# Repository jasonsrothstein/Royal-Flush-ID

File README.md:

# Royal-Flush-ID
Purdue University ECE 477 
Spring 2019 Senior Design 
Group 21

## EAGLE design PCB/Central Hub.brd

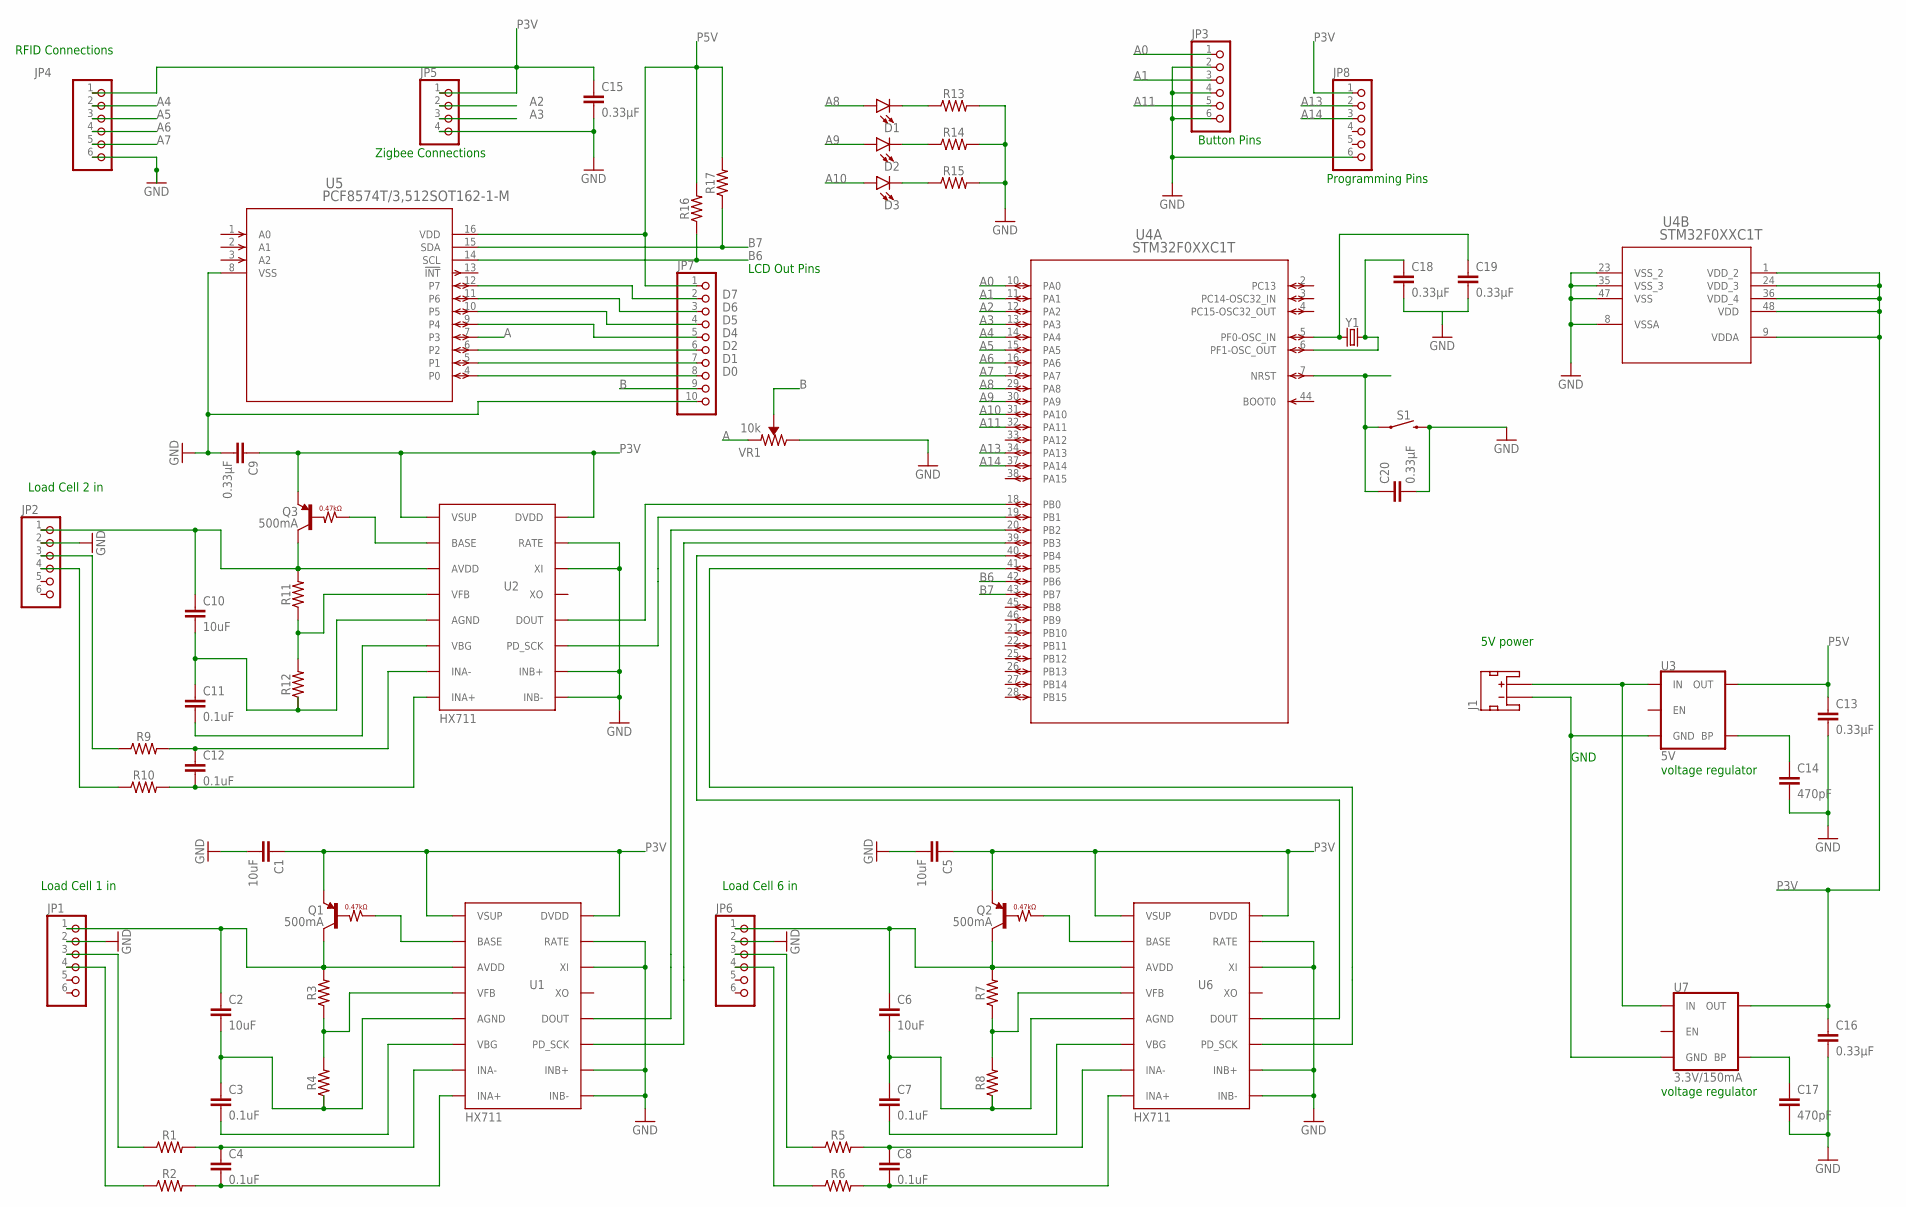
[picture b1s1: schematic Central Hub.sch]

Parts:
C1, C2, C5, C6, C10: 10uF; 0603
C3, C4, C7, C8, C11, C12: 0.1uF; 0603
C9, C13, C15, C16, C18, C19, C20: 0.33µF; 0805
C14, C17: 470pF; 0603
D1, D2, D3: LED5MM; LED_5MM
J1: JST_2MM_MALE; JST-2-SMD
JP1, JP2, JP3, JP4, JP6, JP8: PINHD-1X6; 1X06
JP5: PINHD-1X4; 1X04
JP7: PINHD-1X10; 1X10
Q1, Q2, Q3: 500mA; SOT23-3
R1, R2, R3, R4, R5, R6, R7, R8, R9, R10, R11, R12, R13, R14, R15, R16, R17: 0603
S1: MOMENTARY-SWITCH-SPST-SMD-5.2MM; TACTILE_SWITCH_SMD_5.2MM
U1, U2, U6: HX711; SO16
U3: 5V; SOT23-5
U4: STM32F0XXC1T; LQFP48-7X7MM
U5: PCF8574T/3,512SOT162-1-M; SOT162-1-M
U7: 3.3V/150mA; SOT23-5
VR1: 10k; TRIMPOT-PTH-3386U
Y1: CRYSTALPTH-HC49US; HC49US

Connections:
A: U5.7 (P3), VR1.1 (CCW)
A0: JP3.1, U4.10 (PA0)
A1: JP3.3, U4.11 (PA1)
A2: JP5.2, U4.12 (PA2)
A3: JP5.3, U4.13 (PA3)
A4: JP4.2, U4.14 (PA4)
A5: JP4.3, U4.15 (PA5)
A6: JP4.4, U4.16 (PA6)
A7: JP4.5, U4.17 (PA7)
A8: D1.A, U4.29 (PA8)
A9: D2.A, U4.30 (PA9)
A10: D3.A, U4.31 (PA10)
A11: JP3.5, U4.32 (PA11)
A13: JP8.2, U4.34 (PA13)
A14: JP8.3, U4.37 (PA14)
B: JP7.9, VR1.2 (WIPER)
B6: R16.1, U4.42 (PB6), U5.14 (SCL)
B7: R17.1, U4.43 (PB7), U5.15 (SDA)
D0: JP7.8, U5.4 (P0)
D1: JP7.7, U5.5 (P1)
D2: JP7.6, U5.6 (P2)
D4: JP7.5, U5.9 (P4)
D5: JP7.4, U5.10 (P5)
D6: JP7.3, U5.11 (P6)
D7: JP7.2, U5.12 (P7)
GND: C1.2, C5.2, C9.2, C13.2, C14.2, C15.2, C16.2, C17.2, C18.2, C19.2, C20.2, JP1.2, JP2.2, JP3.2, JP3.4, JP3.6, JP4.6, JP5.4, JP6.2, JP7.10, JP8.6, R13.2, R14.2, R15.2, S1.3 (2), U1.9 (INB-), U1.10 (INB+), U1.14 (XI), U1.15 (RATE), U2.9 (INB-), U2.10 (INB+), U2.14 (XI), U2.15 (RATE), U4.8 (VSSA), U4.23 (VSS_2), U4.35 (VSS_3), U4.47 (VSS), U5.8 (VSS), U6.9 (INB-), U6.10 (INB+), U6.14 (XI), U6.15 (RATE), VR1.3 (CW)
unnamed: C20.1, S1.1, U4.7 (NRST)
unnamed: JP1.3, R1.1
unnamed: JP1.4, R2.1
unnamed: C4.1, R1.2, U1.7 (INA-)
unnamed: C4.2, R2.2, U1.8 (INA+)
unnamed: Q1.1 (B), U1.2 (BASE)
unnamed: C2.1, JP1.1, Q1.3 (C), R3.2, U1.3 (AVDD)
unnamed: C2.2, C3.1, R4.1, U1.5 (AGND)
unnamed: R3.1, R4.2, U1.4 (VFB)
unnamed: C3.2, U1.6 (VBG)
unnamed: JP6.3, R5.1
unnamed: JP6.4, R6.1
unnamed: C8.1, R5.2, U6.7 (INA-)
unnamed: C8.2, R6.2, U6.8 (INA+)
unnamed: Q2.1 (B), U6.2 (BASE)
unnamed: C6.1, JP6.1, Q2.3 (C), R7.2, U6.3 (AVDD)
unnamed: C6.2, C7.1, R8.1, U6.5 (AGND)
unnamed: R7.1, R8.2, U6.4 (VFB)
unnamed: C7.2, U6.6 (VBG)
unnamed: C19.1, U4.5 (PF0-OSC_IN), Y1.1
unnamed: C18.1, U4.6 (PF1-OSC_OUT), Y1.2
unnamed: JP2.3, R9.1
unnamed: JP2.4, R10.1
unnamed: C12.1, R9.2, U2.7 (INA-)
unnamed: C12.2, R10.2, U2.8 (INA+)
unnamed: Q3.1 (B), U2.2 (BASE)
unnamed: C10.1, JP2.1, Q3.3 (C), R11.2, U2.3 (AVDD)
unnamed: C10.2, C11.1, R12.1, U2.5 (AGND)
unnamed: R11.1, R12.2, U2.4 (VFB)
unnamed: C11.2, U2.6 (VBG)
unnamed: J1.1 (-), U3.2 (GND), U7.2 (GND)
unnamed: C17.1, U7.4 (BP)
unnamed: C14.1, U3.4 (BP)
unnamed: J1.2 (+), U3.1 (IN), U7.1 (IN)
unnamed: D1.K (C), R13.1
unnamed: D2.K (C), R14.1
unnamed: D3.K (C), R15.1
unnamed: U4.41 (PB5), U6.11 (PD_SCK)
unnamed: U4.40 (PB4), U6.12 (DOUT)
unnamed: U1.11 (PD_SCK), U4.39 (PB3)
unnamed: U1.12 (DOUT), U4.20 (PB2)
unnamed: U2.11 (PD_SCK), U4.19 (PB1)
unnamed: U2.12 (DOUT), U4.18 (PB0)
P3V: C1.1, C5.1, C9.1, C15.1, C16.1, JP4.1, JP5.1, JP8.1, Q1.2 (E), Q2.2 (E), Q3.2 (E), U1.1 (VSUP), U1.16 (DVDD), U2.1 (VSUP), U2.16 (DVDD), U4.1 (VDD_2), U4.9 (VDDA), U4.24 (VDD_3), U4.36 (VDD_4), U4.48 (VDD), U6.1 (VSUP), U6.16 (DVDD), U7.5 (OUT)
P5V: C13.1, JP7.1, R16.2, R17.2, U3.5 (OUT), U5.16 (VDD)

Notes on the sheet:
Zigbee Connections
RFID Connections
voltage regulator
5V power
GND
Programming Pins
Button Pins
LCD Out Pins
Load Cell 2 in
Load Cell 1 in
Load Cell 6 in

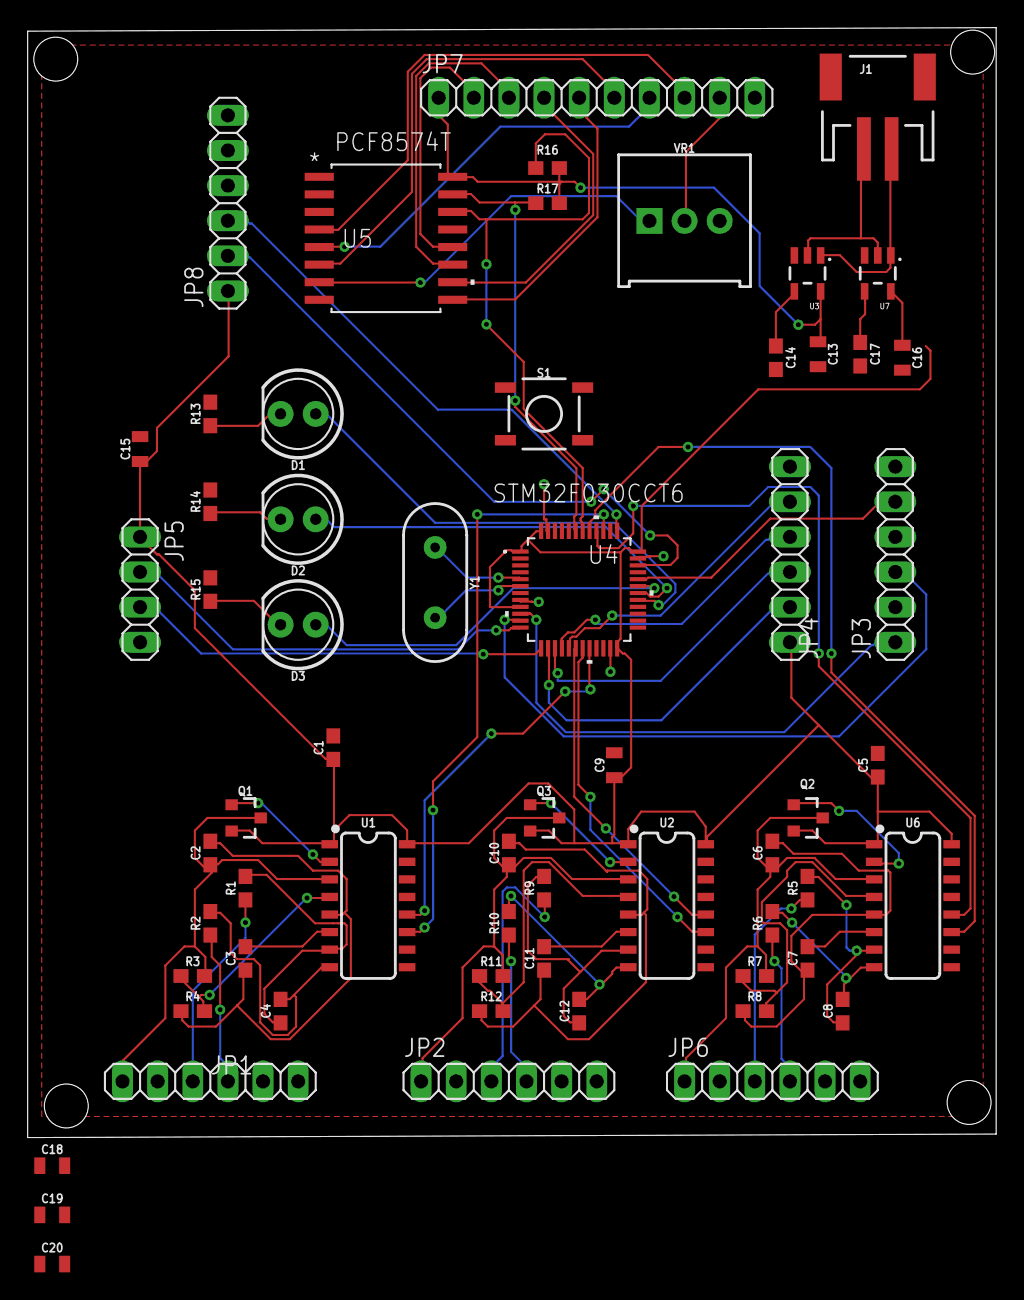
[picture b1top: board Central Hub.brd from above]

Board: 2 copper layers, 70.0 x 80.3 mm, 62 parts (0 on the bottom side), 71 nets.

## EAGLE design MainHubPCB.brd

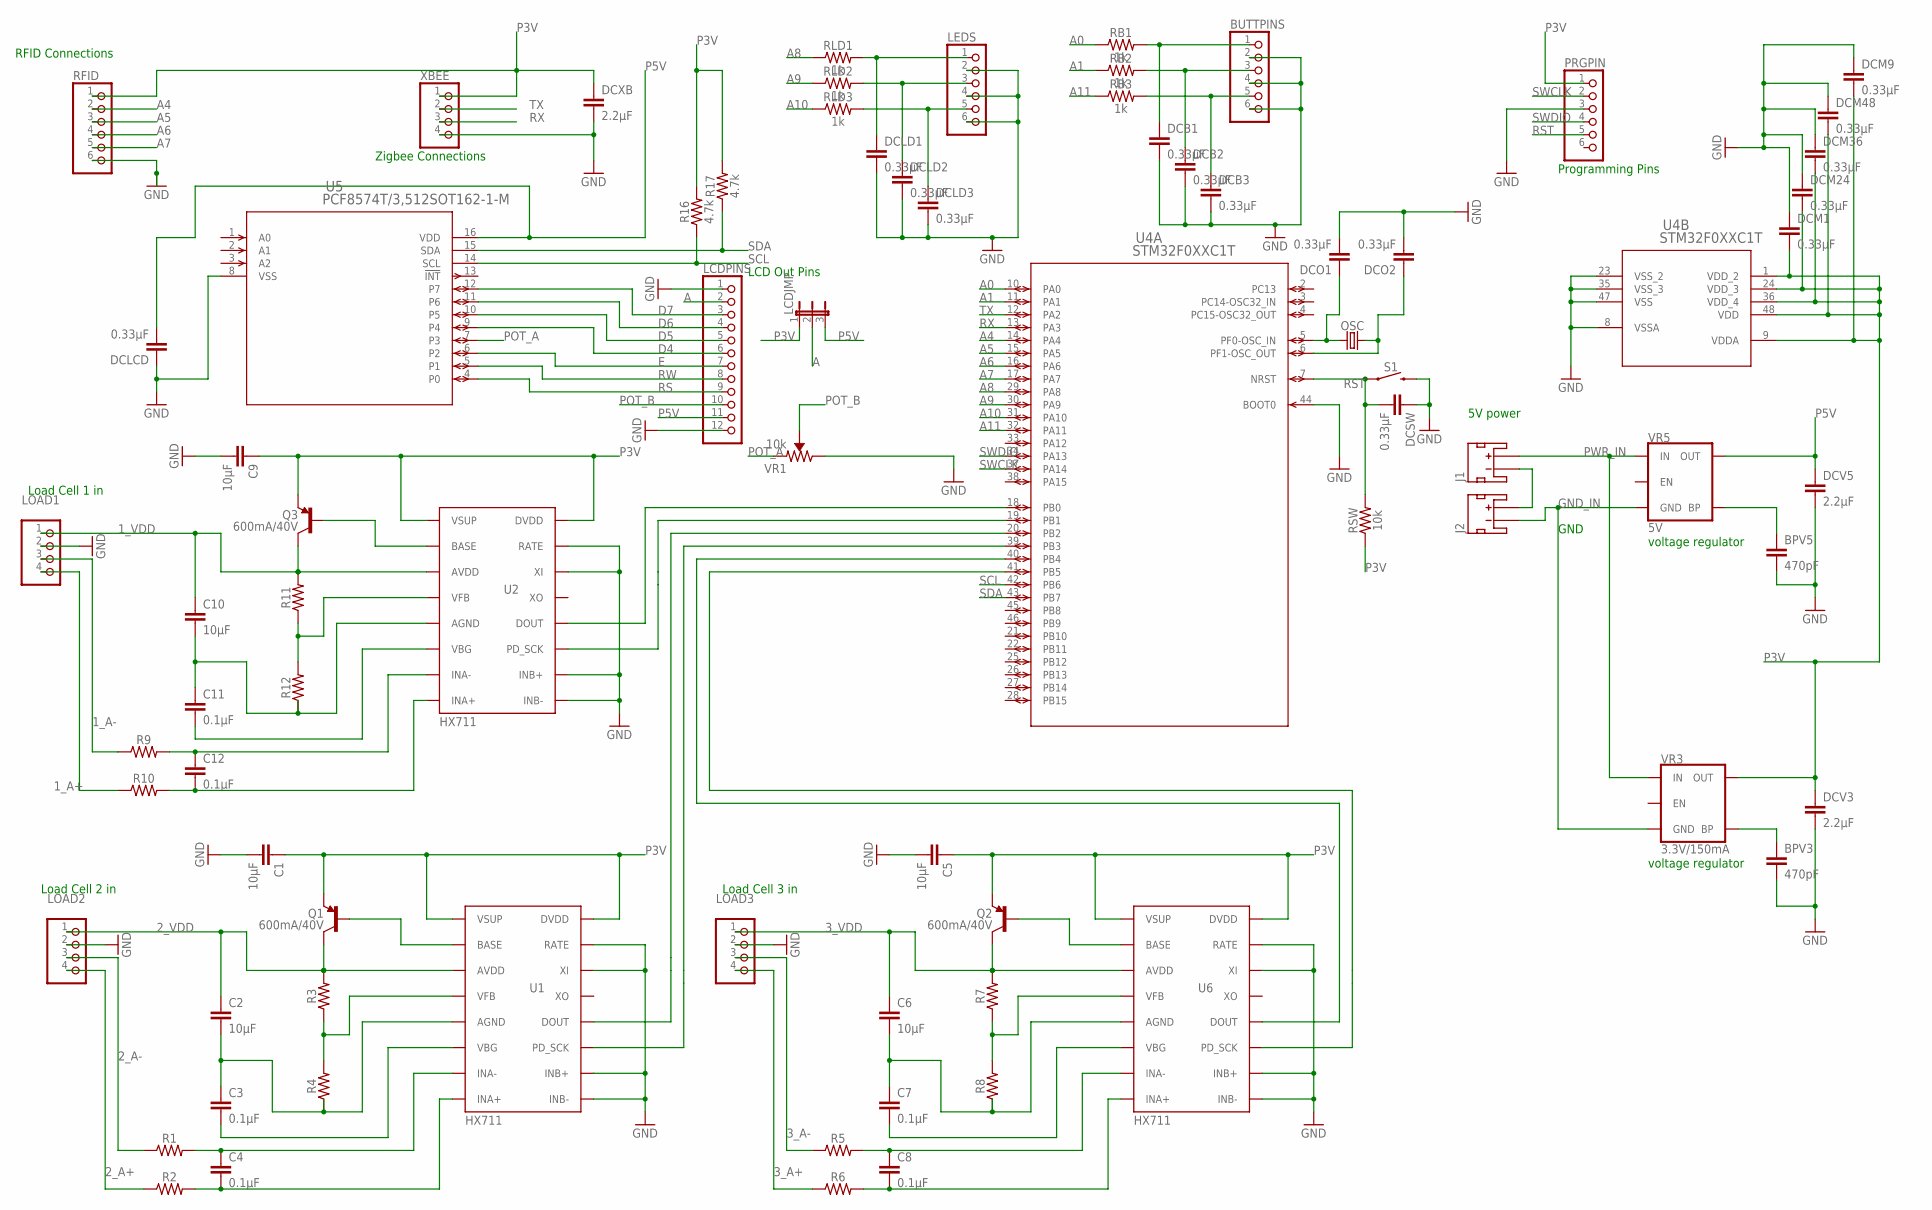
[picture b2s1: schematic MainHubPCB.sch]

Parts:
BPV3, BPV5: 470pF; 0805
BUTTPINS: PINHD-1X6; 1X06
C1, C2, C5, C6, C9, C10: 10µF; 0805
C3, C4, C7, C8, C11, C12: 0.1µF; 0805
DCB1, DCB2, DCB3: 0.33µF; 0805
DCLCD: 0.33µF; 0805
DCLD1, DCLD2, DCLD3: 0.33µF; 0805
DCM1, DCM9, DCM24, DCM36, DCM48: 0.33µF; 0805
DCO1, DCO2: 0.33µF; 0805
DCSW: 0.33µF; 0805
DCV3, DCV5: 2.2µF; 0805
DCXB: 2.2µF; 0805
J1, J2: JST_2MM_MALE; JST-2-SMD
LCDJMP: JP2E; JP2
LCDPINS: PINHD-1X12; 1X12
LEDS: PINHD-1X6; 1X06
LOAD1, LOAD2, LOAD3: PINHD-1X4; 1X04
OSC: CRYSTALPTH-HC49US; HC49US
PRGPIN: PINHD-1X6; 1X06
Q1, Q2, Q3: 600mA/40V; SOT23-3
R1, R2, R3, R4, R5, R6, R7, R8, R9, R10, R11, R12: 0805
R16, R17: 4.7k; 0805
RB1, RB2, RB3: 1k; 0805
RFID: PINHD-1X6; 1X06
RLD1, RLD2, RLD3: 1k; 0805
RSW: 10k; 0805
S1: MOMENTARY-SWITCH-SPST-SMD-5.2MM; TACTILE_SWITCH_SMD_5.2MM
U1, U2, U6: HX711; SO16
U4: STM32F0XXC1T; LQFP48-7X7MM
U5: PCF8574T/3,512SOT162-1-M; SOT162-1-M
VR1: 10k; TRIMPOT-PTH-3386U
VR3: 3.3V/150mA; SOT23-5
VR5: 5V; SOT23-5
XBEE: PINHD-1X4; 1X04

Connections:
1_A+: LOAD1.4, R10.1
1_A-: LOAD1.3, R9.1
1_VDD: C10.1, LOAD1.1, Q3.3 (C), R11.2, U2.3 (AVDD)
2_A+: LOAD2.4, R2.1
2_A-: LOAD2.3, R1.1
2_VDD: C2.1, LOAD2.1, Q1.3 (C), R3.2, U1.3 (AVDD)
3_A+: LOAD3.4, R6.1
3_A-: LOAD3.3, R5.1
3_VDD: C6.1, LOAD3.1, Q2.3 (C), R7.2, U6.3 (AVDD)
A: LCDJMP.2, LCDPINS.2
A0: RB1.1, U4.10 (PA0)
A1: RB2.1, U4.11 (PA1)
A4: RFID.2, U4.14 (PA4)
A5: RFID.3, U4.15 (PA5)
A6: RFID.4, U4.16 (PA6)
A7: RFID.5, U4.17 (PA7)
A8: RLD1.1, U4.29 (PA8)
A9: RLD2.1, U4.30 (PA9)
A10: RLD3.1, U4.31 (PA10)
A11: RB3.1, U4.32 (PA11)
D4: LCDPINS.6, U5.9 (P4)
D5: LCDPINS.5, U5.10 (P5)
D6: LCDPINS.4, U5.11 (P6)
D7: LCDPINS.3, U5.12 (P7)
E: LCDPINS.7, U5.6 (P2)
GND: BPV3.2, BPV5.2, BUTTPINS.2, BUTTPINS.4, BUTTPINS.6, C1.2, C5.2, C9.2, DCB1.2, DCB2.2, DCB3.2, DCLCD.1, DCLD1.2, DCLD2.2, DCLD3.2, DCM1.1, DCM9.1, DCM24.1, DCM36.1, DCM48.1, DCO1.2, DCO2.2, DCSW.1, DCV3.2, DCV5.2, DCXB.2, LCDPINS.1, LCDPINS.12, LEDS.2, LEDS.4, LEDS.6, LOAD1.2, LOAD2.2, LOAD3.2, PRGPIN.3, RFID.6, S1.3 (2), U1.9 (INB-), U1.10 (INB+), U1.14 (XI), U1.15 (RATE), U2.9 (INB-), U2.10 (INB+), U2.14 (XI), U2.15 (RATE), U4.8 (VSSA), U4.23 (VSS_2), U4.35 (VSS_3), U4.44 (BOOT0), U4.47 (VSS), U5.8 (VSS), U6.9 (INB-), U6.10 (INB+), U6.14 (XI), U6.15 (RATE), VR1.3 (CW), XBEE.4
GND_IN: J2.1 (-), VR3.2 (GND), VR5.2 (GND)
unnamed: J1.1 (-), J2.2 (+)
unnamed: C4.1, R1.2, U1.7 (INA-)
unnamed: C4.2, R2.2, U1.8 (INA+)
unnamed: Q1.1 (B), U1.2 (BASE)
unnamed: C2.2, C3.1, R4.1, U1.5 (AGND)
unnamed: R3.1, R4.2, U1.4 (VFB)
unnamed: DCLD1.1, LEDS.1, RLD1.2
unnamed: C3.2, U1.6 (VBG)
unnamed: C8.1, R5.2, U6.7 (INA-)
unnamed: C8.2, R6.2, U6.8 (INA+)
unnamed: Q2.1 (B), U6.2 (BASE)
unnamed: C6.2, C7.1, R8.1, U6.5 (AGND)
unnamed: R7.1, R8.2, U6.4 (VFB)
unnamed: C7.2, U6.6 (VBG)
unnamed: DCO1.1, OSC.1, U4.5 (PF0-OSC_IN)
unnamed: DCO2.1, OSC.2, U4.6 (PF1-OSC_OUT)
unnamed: C12.1, R9.2, U2.7 (INA-)
unnamed: C12.2, R10.2, U2.8 (INA+)
unnamed: Q3.1 (B), U2.2 (BASE)
unnamed: C10.2, C11.1, R12.1, U2.5 (AGND)
unnamed: R11.1, R12.2, U2.4 (VFB)
unnamed: C11.2, U2.6 (VBG)
unnamed: DCLD2.1, LEDS.3, RLD2.2
unnamed: DCLD3.1, LEDS.5, RLD3.2
unnamed: BPV3.1, VR3.4 (BP)
unnamed: BUTTPINS.1, DCB1.1, RB1.2
unnamed: BUTTPINS.3, DCB2.1, RB2.2
unnamed: BPV5.1, VR5.4 (BP)
unnamed: BUTTPINS.5, DCB3.1, RB3.2
unnamed: U4.41 (PB5), U6.11 (PD_SCK)
unnamed: U4.40 (PB4), U6.12 (DOUT)
unnamed: U1.11 (PD_SCK), U4.39 (PB3)
unnamed: U1.12 (DOUT), U4.20 (PB2)
unnamed: U2.11 (PD_SCK), U4.19 (PB1)
unnamed: U2.12 (DOUT), U4.18 (PB0)
P3V: C1.1, C5.1, C9.1, DCM1.2, DCM9.2, DCM24.2, DCM36.2, DCM48.2, DCV3.1, DCXB.1, LCDJMP.1, PRGPIN.1, Q1.2 (E), Q2.2 (E), Q3.2 (E), R16.2, R17.2, RFID.1, RSW.1, U1.1 (VSUP), U1.16 (DVDD), U2.1 (VSUP), U2.16 (DVDD), U4.1 (VDD_2), U4.9 (VDDA), U4.24 (VDD_3), U4.36 (VDD_4), U4.48 (VDD), U6.1 (VSUP), U6.16 (DVDD), VR3.5 (OUT), XBEE.1
P5V: DCLCD.2, DCV5.1, LCDJMP.3, LCDPINS.11, U5.16 (VDD), VR5.5 (OUT)
POT_A: U5.7 (P3), VR1.1 (CCW)
POT_B: LCDPINS.10, VR1.2 (WIPER)
PWR_IN: J1.2 (+), VR3.1 (IN), VR5.1 (IN)
RS: LCDPINS.9, U5.4 (P0)
RST: DCSW.2, PRGPIN.5, RSW.2, S1.1, U4.7 (NRST)
RW: LCDPINS.8, U5.5 (P1)
RX: U4.13 (PA3), XBEE.3
SCL: R16.1, U4.42 (PB6), U5.14 (SCL)
SDA: R17.1, U4.43 (PB7), U5.15 (SDA)
SWCLK: PRGPIN.2, U4.37 (PA14)
SWDIO: PRGPIN.4, U4.34 (PA13)
TX: U4.12 (PA2), XBEE.2

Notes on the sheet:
Zigbee Connections
RFID Connections
voltage regulator
5V power
GND
Programming Pins
LCD Out Pins
Load Cell 1 in
Load Cell 2 in
Load Cell 3 in

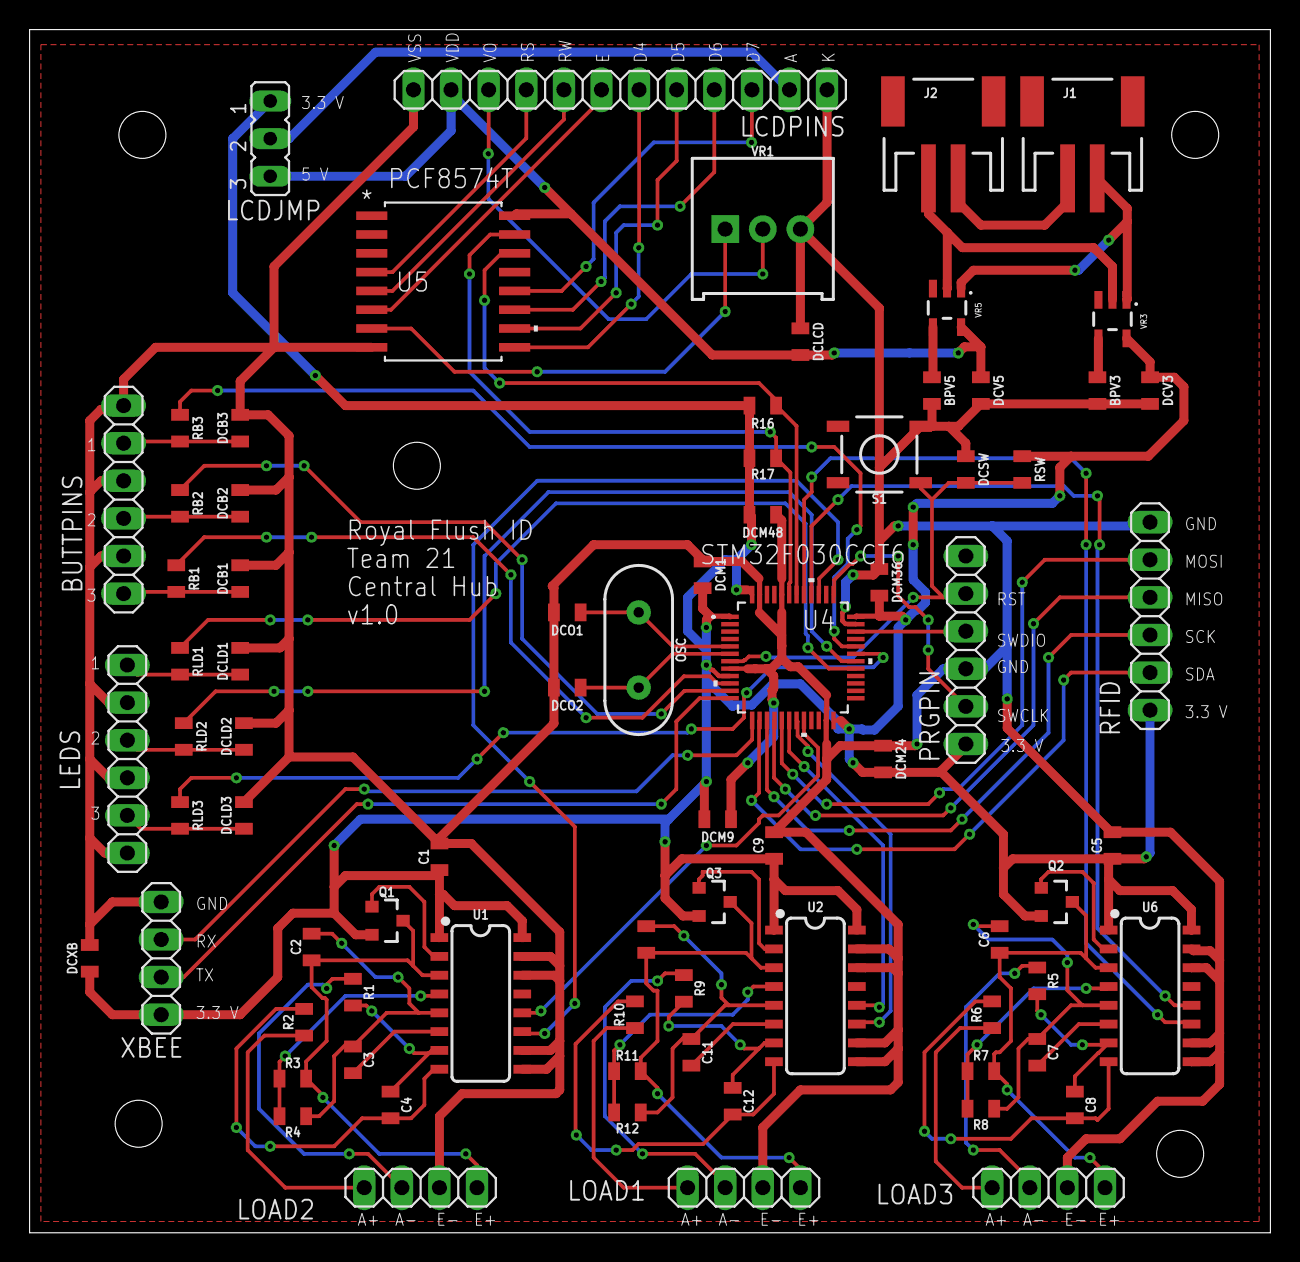
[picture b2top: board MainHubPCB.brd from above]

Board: 2 copper layers, 83.8 x 81.3 mm, 78 parts (0 on the bottom side), 76 nets.

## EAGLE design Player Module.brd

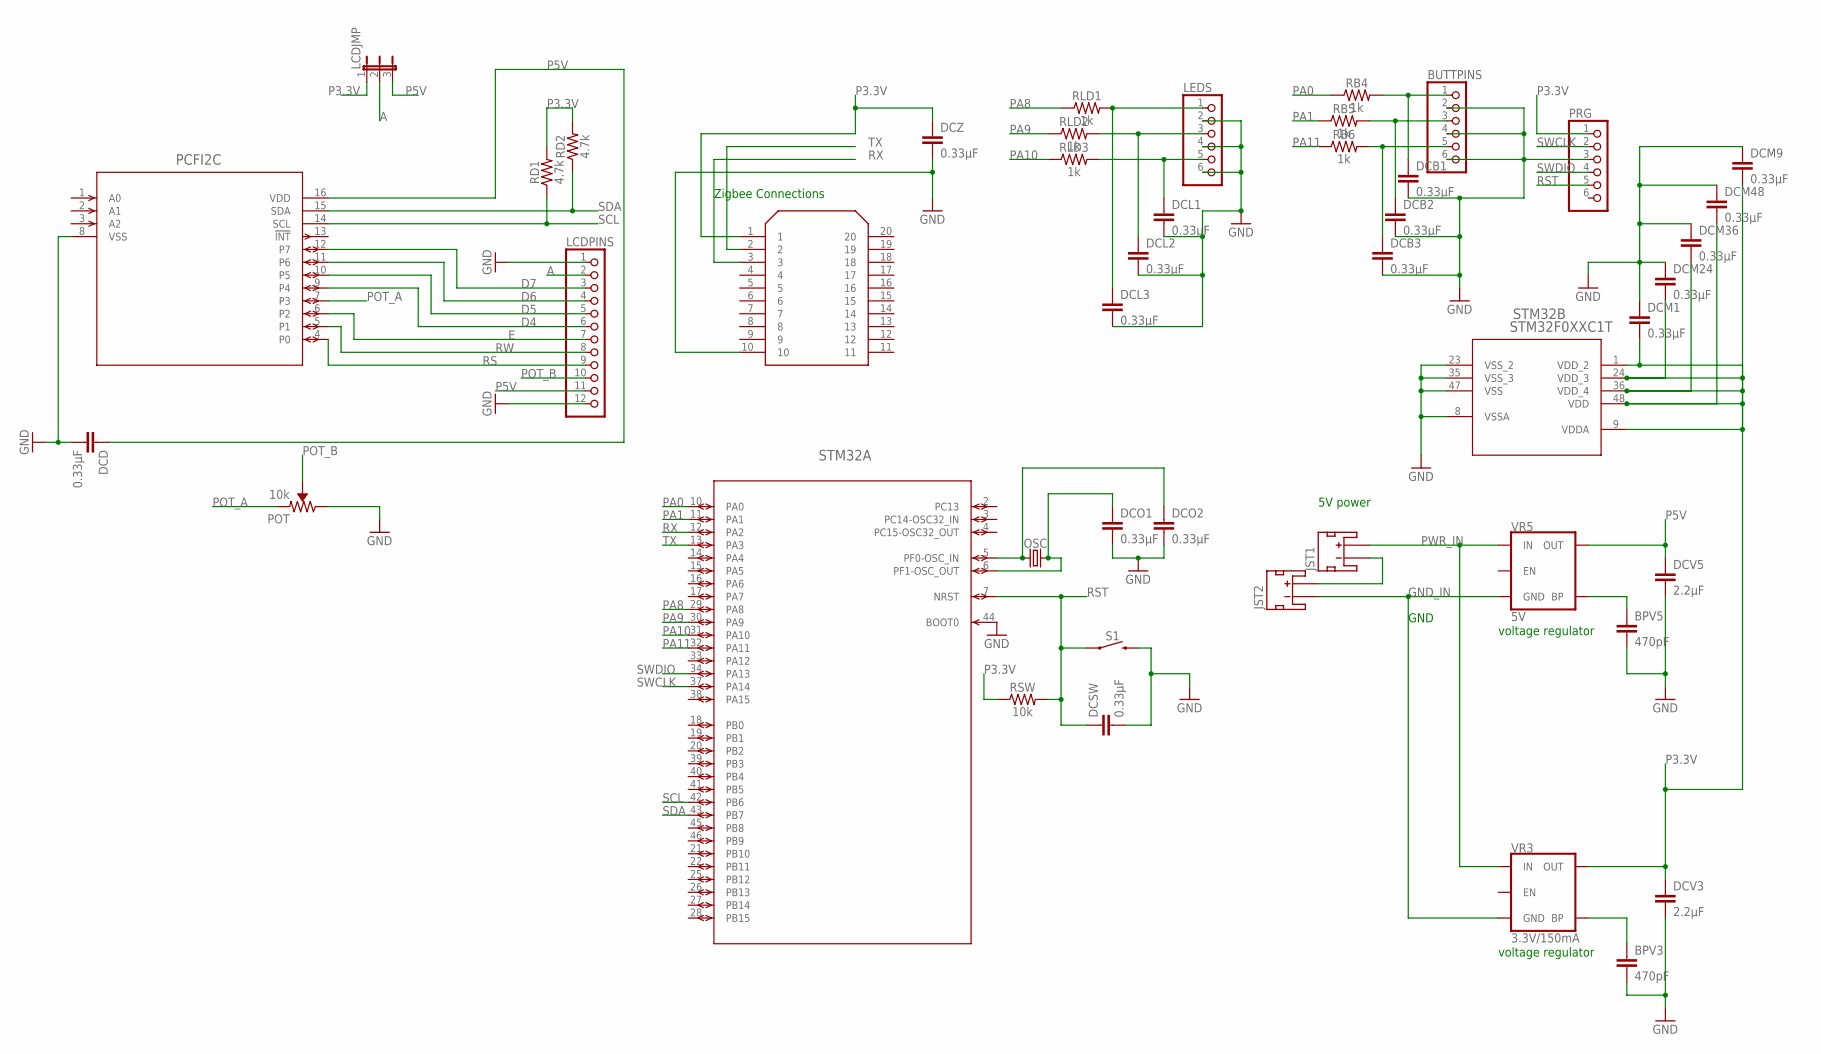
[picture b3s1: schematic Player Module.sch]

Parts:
BPV3, BPV5: 470pF; 0805
BUTTPINS: PINHD-1X6; 1X06
DCB1, DCB2, DCB3: 0.33µF; 0805
DCD: 0.33µF; 0805
DCL1, DCL2, DCL3: 0.33µF; 0805
DCM1, DCM9, DCM24, DCM36, DCM48: 0.33µF; 0805
DCO1, DCO2: 0.33µF; 0805
DCSW: 0.33µF; 0805
DCV3, DCV5: 2.2µF; 0805
DCZ: 0.33µF; 0805
JST1, JST2: JST_2MM_MALE; JST-2-SMD
LCDJMP: JP2E; JP2
LCDPINS: PINHD-1X12; 1X12
LEDS: PINHD-1X6; 1X06
OSC: CRYSTALPTH-HC49US; HC49US
PCFI2C: PCF8574T/3,512SOT162-1-M; SOT162-1-M
POT: 10k; TRIMPOT-PTH-3386U
PRG: PINHD-1X6; 1X06
RB4, RB5, RB6: 1k; 0805
RD1, RD2: 4.7k; 0805
RLD1, RLD2, RLD3: 1k; 0805
RSW: 10k; 0805
S1: MOMENTARY-SWITCH-SPST-SMD-5.2MM; TACTILE_SWITCH_SMD_5.2MM
STM32: STM32F0XXC1T; LQFP48-7X7MM
VR3: 3.3V/150mA; SOT23-5
VR5: 5V; SOT23-5
XBEE: XB24-BPIT-004; DIP-20

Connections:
A: LCDJMP.2, LCDPINS.2
D4: LCDPINS.6, PCFI2C.9 (P4)
D5: LCDPINS.5, PCFI2C.10 (P5)
D6: LCDPINS.4, PCFI2C.11 (P6)
D7: LCDPINS.3, PCFI2C.12 (P7)
E: LCDPINS.7, PCFI2C.6 (P2)
GND: BPV3.2, BPV5.2, BUTTPINS.2, BUTTPINS.4, BUTTPINS.6, DCB1.2, DCB2.2, DCB3.2, DCD.2, DCL1.2, DCL2.2, DCL3.2, DCM1.1, DCM9.1, DCM24.1, DCM36.1, DCM48.1, DCO1.2, DCO2.2, DCSW.2, DCV3.2, DCV5.2, DCZ.2, LCDPINS.1, LCDPINS.12, LEDS.2, LEDS.4, LEDS.6, PCFI2C.8 (VSS), POT.3 (CW), PRG.3, S1.3 (2), STM32.8 (VSSA), STM32.23 (VSS_2), STM32.35 (VSS_3), STM32.44 (BOOT0), STM32.47 (VSS), XBEE.10
GND_IN: JST2.1 (-), VR3.2 (GND), VR5.2 (GND)
unnamed: JST1.1 (-), JST2.2 (+)
unnamed: DCL3.1, LEDS.1, RLD1.2
unnamed: DCL2.1, LEDS.3, RLD2.2
unnamed: DCL1.1, LEDS.5, RLD3.2
unnamed: BUTTPINS.1, DCB1.1, RB4.2
unnamed: BUTTPINS.3, DCB2.1, RB5.2
unnamed: BUTTPINS.5, DCB3.1, RB6.2
unnamed: DCO2.1, OSC.1, STM32.5 (PF0-OSC_IN)
unnamed: DCO1.1, OSC.2, STM32.6 (PF1-OSC_OUT)
unnamed: BPV3.1, VR3.4 (BP)
unnamed: BPV5.1, VR5.4 (BP)
P3.3V: DCM1.2, DCM9.2, DCM24.2, DCM36.2, DCM48.2, DCV3.1, DCZ.1, LCDJMP.1, PRG.1, RD1.2, RD2.2, RSW.1, STM32.1 (VDD_2), STM32.9 (VDDA), STM32.24 (VDD_3), STM32.36 (VDD_4), STM32.48 (VDD), VR3.5 (OUT), XBEE.1
P5V: DCD.1, DCV5.1, LCDJMP.3, LCDPINS.11, PCFI2C.16 (VDD), VR5.5 (OUT)
PA0: RB4.1, STM32.10 (PA0)
PA1: RB5.1, STM32.11 (PA1)
PA8: RLD1.1, STM32.29 (PA8)
PA9: RLD2.1, STM32.30 (PA9)
PA10: RLD3.1, STM32.31 (PA10)
PA11: RB6.1, STM32.32 (PA11)
POT_A: PCFI2C.7 (P3), POT.1 (CCW)
POT_B: LCDPINS.10, POT.2 (WIPER)
PWR_IN: JST1.2 (+), VR3.1 (IN), VR5.1 (IN)
RS: LCDPINS.9, PCFI2C.4 (P0)
RST: DCSW.1, PRG.5, RSW.2, S1.1, STM32.7 (NRST)
RW: LCDPINS.8, PCFI2C.5 (P1)
RX: STM32.12 (PA2), XBEE.3
SCL: PCFI2C.14 (SCL), RD1.1, STM32.42 (PB6)
SDA: PCFI2C.15 (SDA), RD2.1, STM32.43 (PB7)
SWCLK: PRG.2, STM32.37 (PA14)
SWDIO: PRG.4, STM32.34 (PA13)
TX: STM32.13 (PA3), XBEE.2

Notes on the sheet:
Zigbee Connections
voltage regulator
5V power
GND

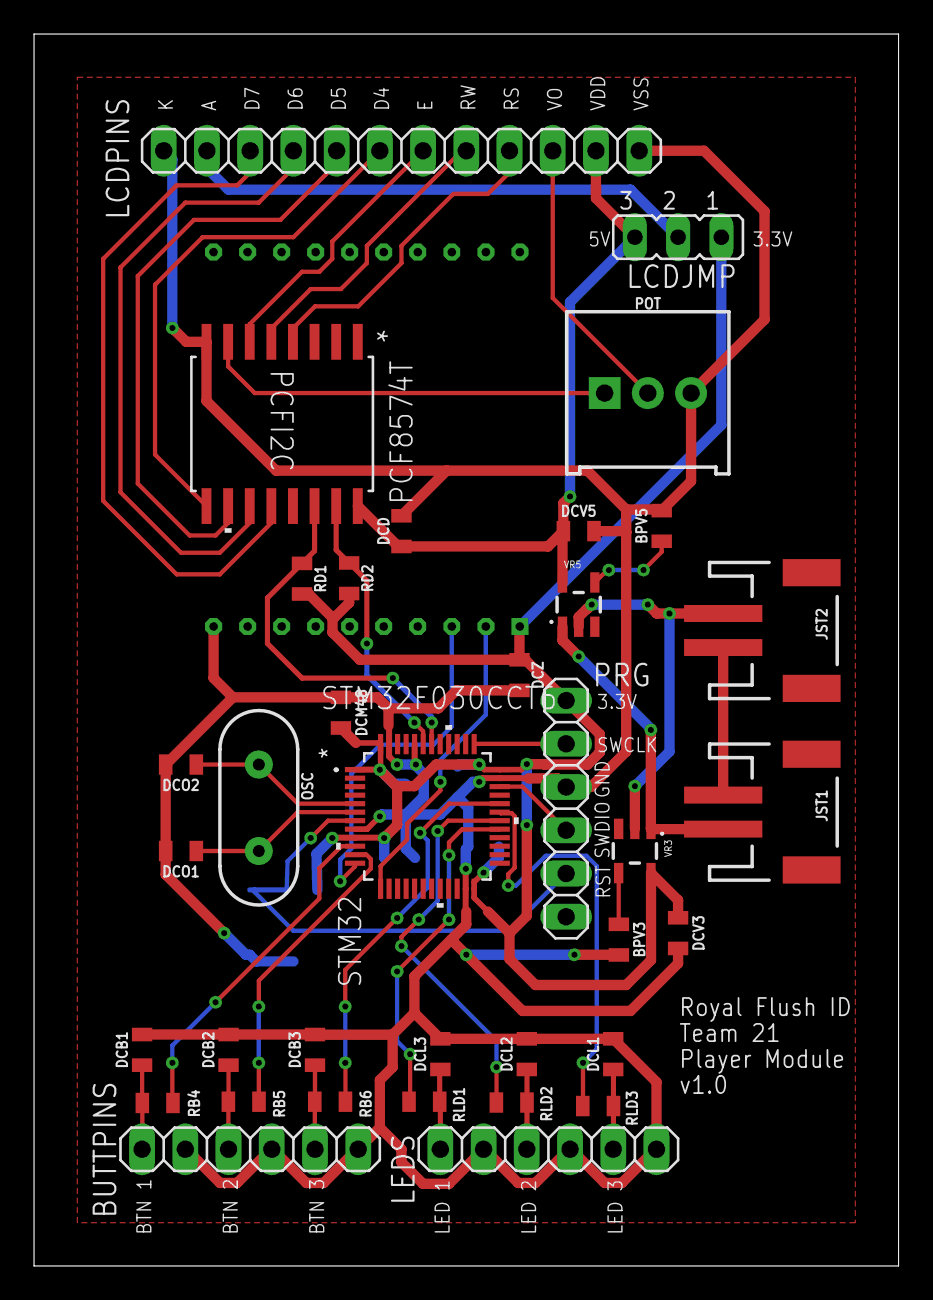
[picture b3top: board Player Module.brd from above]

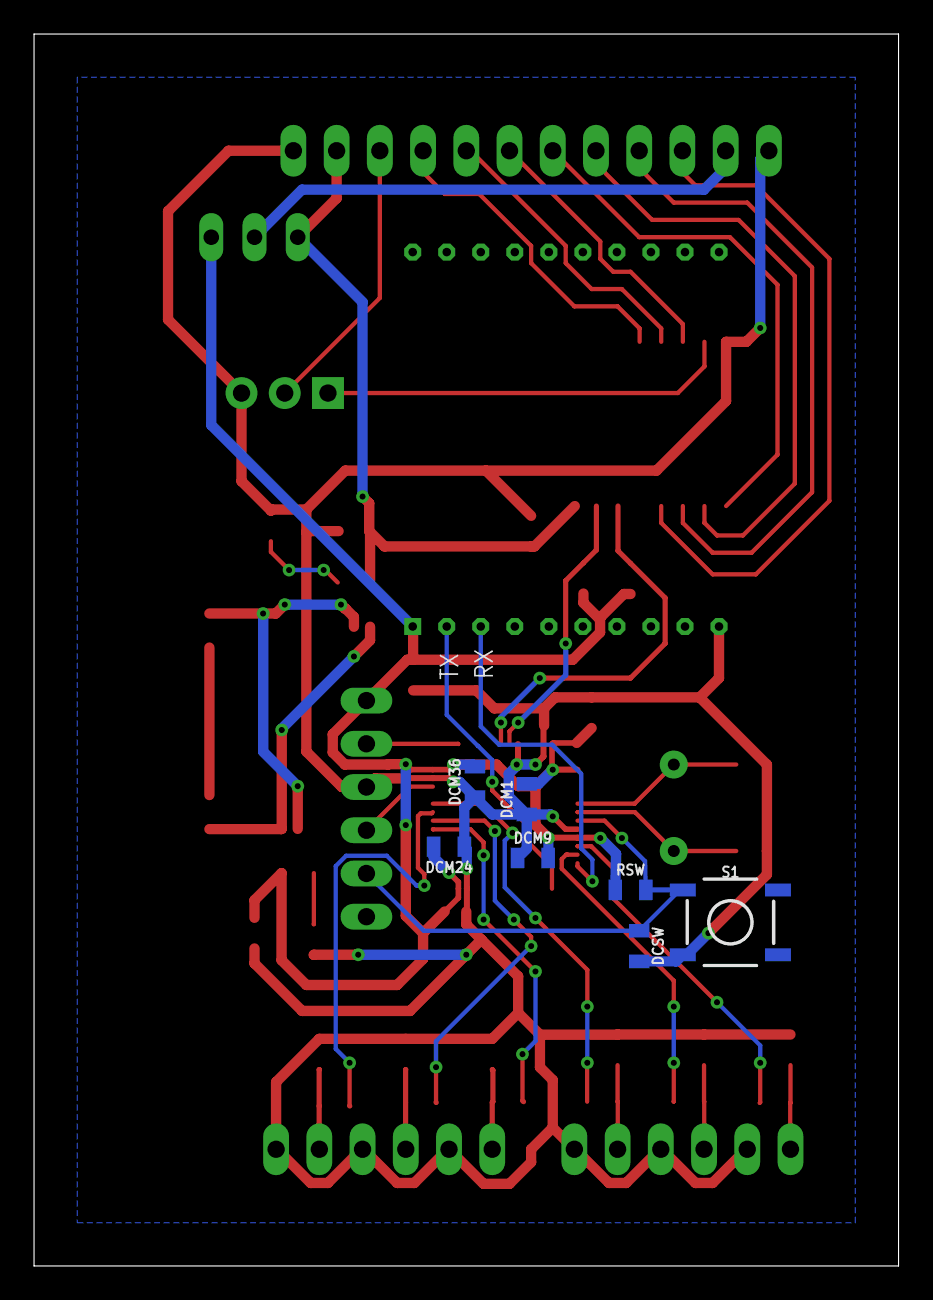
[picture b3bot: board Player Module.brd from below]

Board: 2 copper layers, 50.8 x 72.4 mm, 44 parts (8 on the bottom side), 39 nets.

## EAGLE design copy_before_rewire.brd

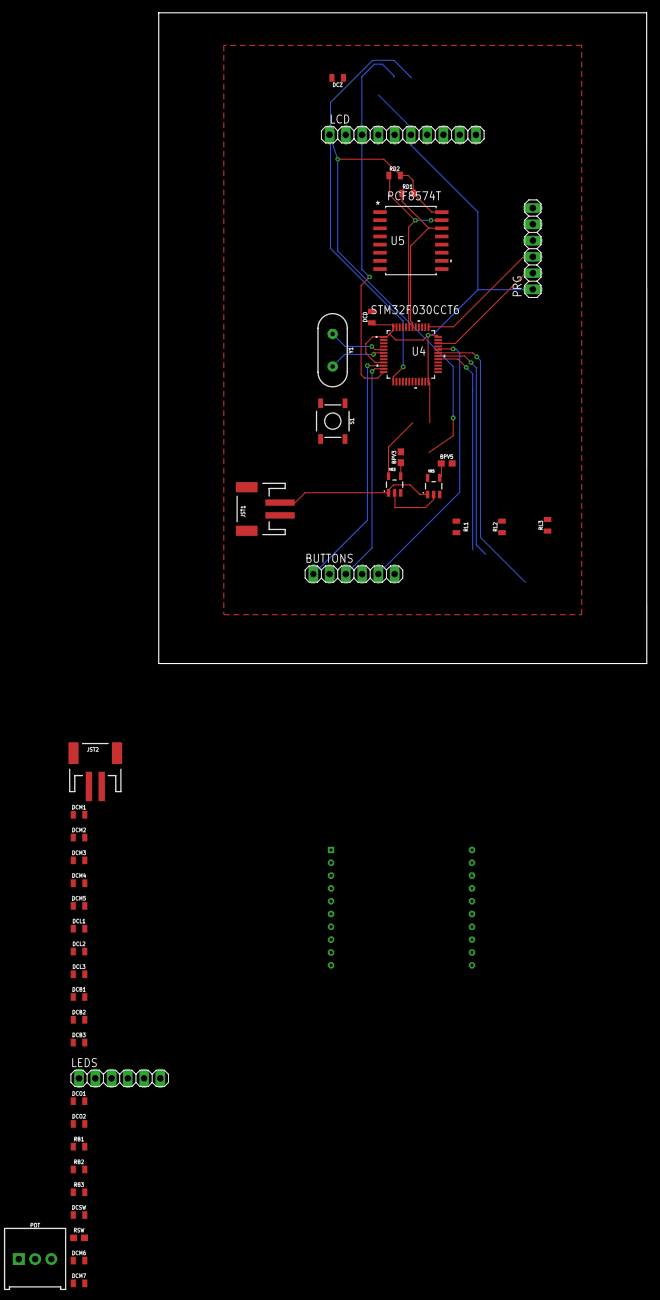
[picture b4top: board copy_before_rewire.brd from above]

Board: 2 copper layers, 76.2 x 101.6 mm, 43 parts (0 on the bottom side), 38 nets.

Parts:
BPV3, BPV5: 470pF; 0603
BUTTONS: 1X06
DCB1, DCB2, DCB3: 0.33µF; 0805
DCD: 0.33µF; 0805
DCL1, DCL2, DCL3: 0.33µF; 0805
DCM1, DCM2, DCM3, DCM4, DCM5, DCM6, DCM7: 0.33µF; 0805
DCO1, DCO2: 0.33µF; 0805
DCSW: 0.33µF; 0805
DCZ: 0.33µF; 0805
JST1, JST2: JST-2-SMD
LCD: 1X10
LEDS: 1X06
POT: 10k; TRIMPOT-PTH-3386U
PRG: 1X06
RB1, RB2, RB3: 0805
RD1, RD2: 0805
RL1, RL2, RL3: 0805
RSW: 10k; 0603
S1: MOMENTARY-SWITCH-SPST-SMD-5.2MM; TACTILE_SWITCH_SMD_5.2MM
U4: STM32F0XXC1T; LQFP48-7X7MM
U5: PCF8574T/3,512SOT162-1-M; SOT162-1-M
U$1: XB24-BPIT-004; DIP-20
VR3: 3.3V/150mA; SOT23-5
VR5: 5V; SOT23-5
Y1: HC49US

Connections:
A0: BUTTONS.1, DCB1.1, U4.10
A1: BUTTONS.3, U4.11
A2: U4.12, U$1.2
A3: U4.13, U$1.3
A8: DCL3.1, LEDS.1, U4.29
A9: DCL2.1, LEDS.3, U4.30
A10: DCL1.1, LEDS.5, U4.31
A11: BUTTONS.5, DCB3.1, U4.32
A13: PRG.2, U4.34
A14: PRG.3, U4.37
B6: RD1.1, U4.42, U5.14
B7: RD2.1, U4.43, U5.15
GND: BPV3.2, BPV5.2, DCB1.2, DCB2.2, DCB3.2, DCD.2, DCL1.2, DCL2.2, DCL3.2, DCM1.1, DCM2.1, DCM3.1, DCM4.1, DCM5.1, DCM6.2, DCM7.2, DCO1.2, DCO2.2, DCSW.2, DCZ.2, LCD.10, POT.3, PRG.6, RB1.2, RB2.2, RB3.2, RL1.2, RL2.2, RL3.2, S1.3, U4.8, U4.23, U4.35, U4.47, U5.8, U$1.10
unnamed: JST1.1, JST2.2
unnamed: BUTTONS.4, RB2.1
unnamed: LEDS.6, RL3.1
unnamed: LEDS.4, RL2.1
unnamed: LEDS.2, RL1.1
unnamed: BUTTONS.2, RB1.1
unnamed: BUTTONS.6, RB3.1
unnamed: LCD.2, U5.12
unnamed: LCD.3, U5.11
unnamed: LCD.4, U5.10
unnamed: LCD.5, U5.9
unnamed: LCD.6, U5.6
unnamed: LCD.7, U5.5
unnamed: LCD.8, U5.4
unnamed: DCO2.1, U4.5, Y1.1
unnamed: DCO1.1, U4.6, Y1.2
unnamed: JST2.1, VR3.2, VR5.2
unnamed: BPV3.1, VR3.4
unnamed: BPV5.1, VR5.4
unnamed: JST1.2, VR3.1, VR5.1
P3.3V: DCM1.2, DCM2.2, DCM3.2, DCM4.2, DCM5.2, DCM7.1, DCZ.1, PRG.1, RSW.1, U4.1, U4.9, U4.24, U4.36, U4.48, U$1.1, VR3.5
P5V: DCD.1, DCM6.1, LCD.1, RD1.2, RD2.2, U5.16, VR5.5
POT_A: POT.1, U5.7
POT_B: LCD.9, POT.2
RST: DCSW.1, RSW.2, S1.1, U4.7

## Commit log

2019-02-12 Rename main.c to LCD/reference_code.c
2019-02-23 Add files via upload
    Main Hub Eagle Schematic Files v.1
2019-02-25 player module
2019-02-25 joes boards
2019-03-05 Create led_blink
2019-03-05 Update led_blink
2019-03-05 Create led_btn
2019-03-05 Update led_btn
2019-03-06 Create cmd_switching
2019-03-07 updates as of wednesday night
2019-03-08 Add files via upload
    Final Main Hub PCB schematic and layout to be checked
2019-03-09 final stuff
2019-03-09 final boards
2019-04-03 Rename rfid.h to RFID/rfid.h
2019-04-16 Create Poker
2019-04-16 Create led_btn_test
2019-04-16 Rename led_btn_test to led_btn_test.c
2019-04-16 Rename Player Module.brd to PCB/Player Module.brd
2019-04-16 Rename Central Hub.brd to PCB/Central Hub.brd
2019-04-16 Rename copy_before_rewire.sch to PCB/copy_before_rewire.sch
2019-04-16 Rename Schematic1.s#1 to PCB/Schematic1.s#1
2019-04-16 Rename Central Hub.sch to PCB/Central Hub.sch
2019-04-16 Rename DRILEGEND.CFG to PCB/DRILEGEND.CFG
2019-04-16 Rename MainHubPCB.brd to PCB/MainHubPCB.brd
2019-04-16 Rename MainHubPCB.sch to PCB/MainHubPCB.sch
2019-04-16 Rename Player Module.sch to PCB/Player Module.sch
2019-04-16 Rename Schematic1.brd to PCB/Schematic1.brd
2019-04-16 Rename Schematic1.sch to PCB/Schematic1.sch
2019-04-16 Rename Schematic1_autorouted.brd to PCB/Schematic1_autorouted.brd
2019-04-16 Rename copy_before_rewire.brd to PCB/copy_before_rewire.brd
2019-04-22 Create new_btns
2019-04-22 Update new_btns
2019-04-24 Create PSSC_Code
2019-05-01 hoping these are right - jason

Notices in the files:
parts and their libraries:
SparkFun-IC-Conversion: Licensing: Creative Commons ShareAlike 4.0 International - https://creativecommons.org/licenses/by-sa/4.0
